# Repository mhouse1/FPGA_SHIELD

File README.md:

# FPGA_SHIELD
An awsome shield that supports multiple tranceivers

* Main schematic view

* board layout

* board model view 1

* board model view 2

* control board with relays

* assembled

* lora radios

note: must adjust converters before powering on level shifting circuit, burned out the chip forgetting that on the first board.

changes for next version:
* xt60 wrong polarity
* ~~usb wrong polarity~~
* ~~usb flush mounting ( add holes for protruding USB pins)~~
* adjust J3 position (De nano power input)
* adjust JP2 position 
* add footprint for non PCB XT60
* adjust J6, J7, J10, J1, J2 position spacing to be same as J15, and J16 that way two or 3 position screw terminals can be used
* replace tantlum capacitors with ceramic capacitors?, replace with surface mount caps for easier assembly
* replace with surface mount resistors 
* move J11 and U8 to above JP1 so relay module is inline with PCB giving an overall smaller footprint for control board.
remove JP3
* delete/remove lora module
* add LM1085ISX-ADJ/NOPB or something similar for regulating power going to the USB converter
* add mini fuse, use keystone 3568
* replace terminal blocks with ED100/2DS	,

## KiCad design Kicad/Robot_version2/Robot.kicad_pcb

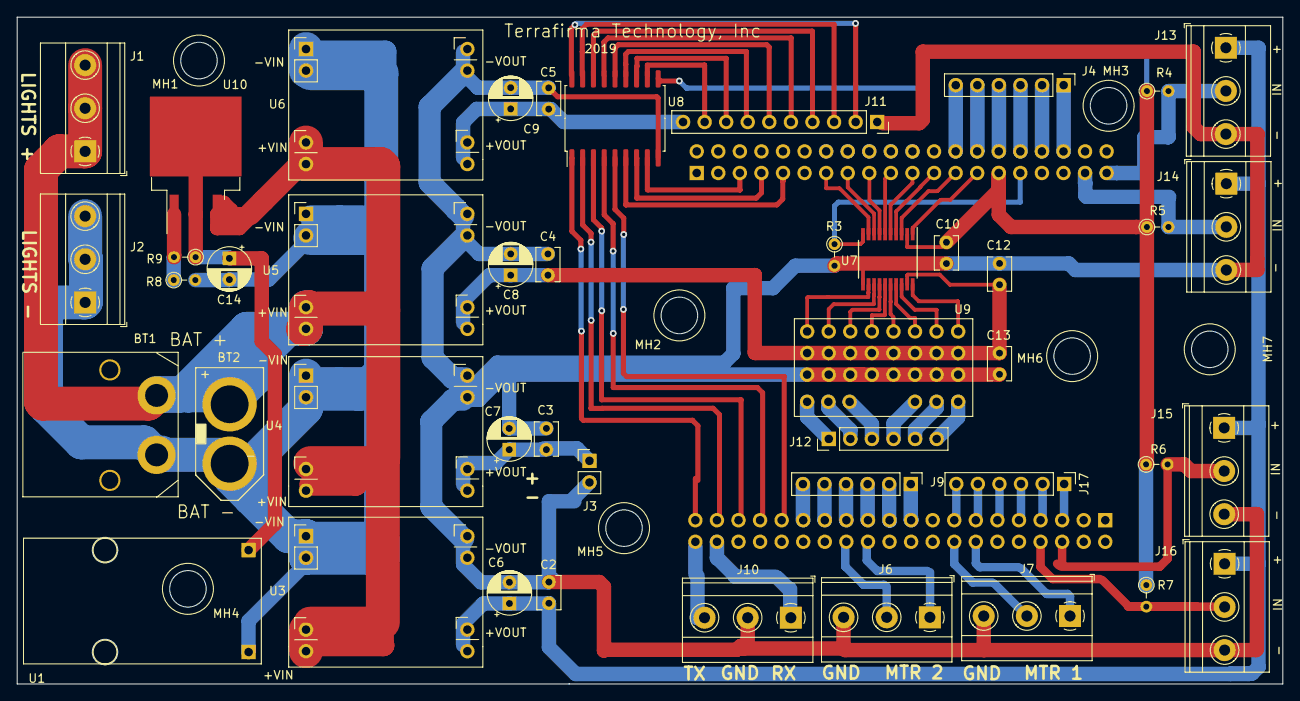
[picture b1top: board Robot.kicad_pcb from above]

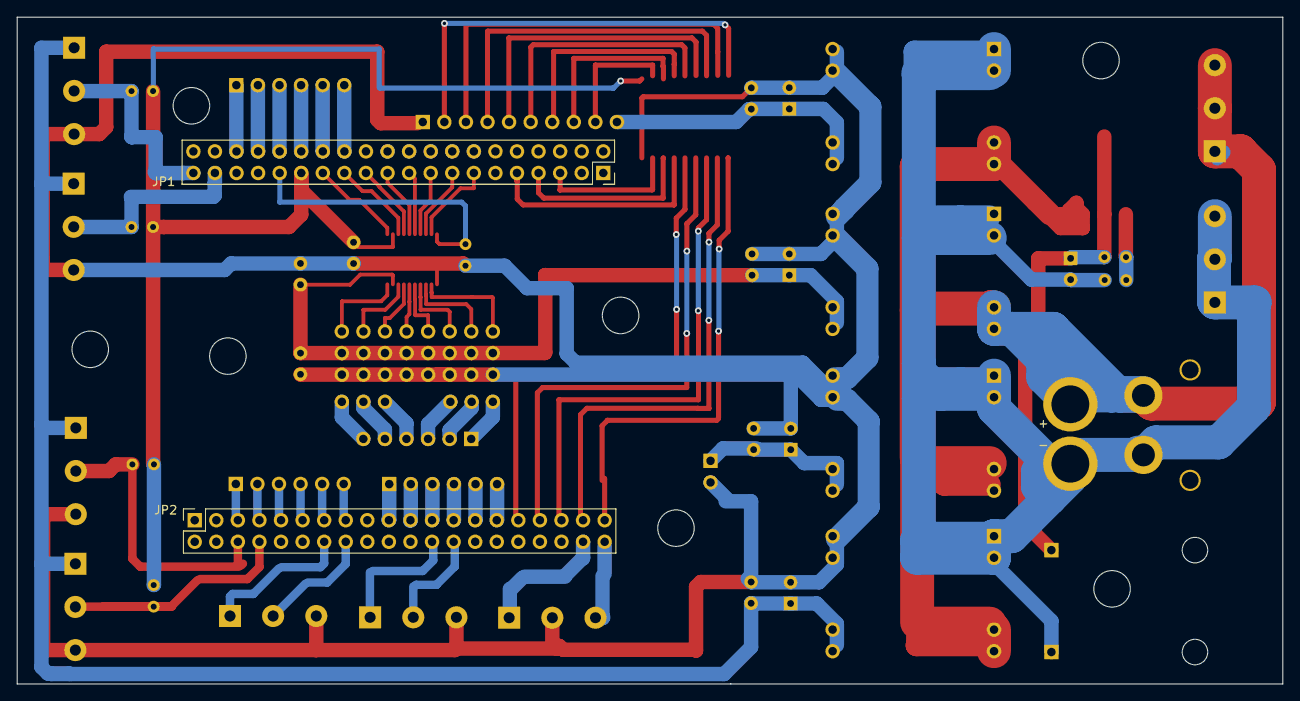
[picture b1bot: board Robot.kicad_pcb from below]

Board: 2 copper layers, 149.0 x 78.5 mm, 54 parts (2 on the bottom side), 77 nets.

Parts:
BT1: Battery_Cell; XT60PW
BT2: Battery_Cell; XT60_M
C2, C3, C4, C5, C10, C12, C13: .1uf; C_Disc_D3.8mm_W2.6mm_P2.50mm
C6, C7, C8, C9, C14: CP1; CP_Radial_D5.0mm_P2.50mm
J1: PositiveBus; TerminalBlock_Phoenix_MKDS-1,5-3-5.08_1x03_P5.08mm_Horizont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
J2: NegativeBus; TerminalBlock_Phoenix_MKDS-1,5-3-5.08_1x03_P5.08mm_Horizont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
J3: PIN HEADER DE0-NANO POWER; PinHeader_1x02_P2.54mm_Vertical
J4, J9, J17: BreakoutHeader; PinHeader_1x06_P2.54mm_Vertical
J6: MotorDriver1; TerminalBlock_Phoenix_MKDS-1,5-3-5.08_1x03_P5.08mm_Horizont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
J7: MotorDriver2; TerminalBlock_Phoenix_MKDS-1,5-3-5.08_1x03_P5.08mm_Horizont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
J10: LORA; TerminalBlock_Phoenix_MKDS-1,5-3-5.08_1x03_P5.08mm_Horizont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
J11: RELAY HEADER; PinSocket_1x10_P2.54mm_Vertical
J12: X8R HEADER; PinHeader_1x06_P2.54mm_Vertical
J13: SENSOR 1; TerminalBlock_Phoenix_MKDS-1,5-3-5.08_1x03_P5.08mm_Horizont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
J14: SENSOR 2; TerminalBlock_Phoenix_MKDS-1,5-3-5.08_1x03_P5.08mm_Horizont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
J15: SENSOR 3; TerminalBlock_Phoenix_MKDS-1,5-3-5.08_1x03_P5.08mm_Horizont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
J16: SENSOR 4; TerminalBlock_Phoenix_MKDS-1,5-3-5.08_1x03_P5.08mm_Horizont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
JP1, JP2: Altera 40 pin connector; PinSocket_2x20_P2.54mm_Vertical
MH1, MH2, MH3, MH4, MH5, MH6, MH7: MountingHole; MountingHole_4.3mm_M4
R3, R4, R5, R6, R7, R8, R9: 4.7K; R_Axial_DIN0204_L3.6mm_D1.6mm_P2.54mm_Vertical
U1: USB_POWER; USB_POWER_flush
U3, U4, U5, U6: Generic_DC_to_DC_Module; GEN_DC_TO_DC
U7: TXS0108E; TSSOP-20_4.4x6.5mm_P0.65mm
U8: TDB62381A; SOIC-18W_7.5x11.6mm_P1.27mm
U9: X8R_Receiver; X8R
U10: LM1085-ADJ; TO-263-3_TabPin2

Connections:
GND: C2.2, C3.2, C4.2, C5.2, C6.2, C7.2, C8.2, C9.2, C10.2, C12.2, C13.2, J3.2, J6.3, J7.3, J10.2, J11.1, J13.3, J14.3, J15.3, J16.3, R3.2, U3.5, U3.6, U4.5, U4.6, U5.5, U5.6, U6.5, U6.6, U7.11, U8.9, U9.17, U9.18, U9.19, U9.20, U9.21, U9.22, U9.23, U9.24
unnamed: BT1.1, BT2.1, C14.2, J2.1, J2.2, J2.3, R8.2, U1.2, U3.1, U3.2, U4.1, U4.2, U5.1, U5.2, U6.1, U6.2
unnamed: BT1.2, BT2.2, J1.1, J1.2, J1.3, U3.3, U3.4, U4.3, U4.4, U5.3, U5.4, U6.3, U6.4, U10.3
unnamed: C3.1, C7.1, J3.1, U4.7, U4.8
unnamed: C14.1, R9.1, U1.1, U10.2
unnamed: J4.1, JP1.36
unnamed: J4.2, JP1.34
unnamed: J4.3, JP1.32
unnamed: J4.4, JP1.30
unnamed: J4.5, JP1.28
unnamed: J4.6, JP1.26
unnamed: J6.1, JP2.14
unnamed: J6.2, JP2.16
unnamed: J7.1, JP2.24
unnamed: J7.2, JP2.26
unnamed: J9.1, JP2.19
unnamed: J9.2, JP2.21
unnamed: J9.3, JP2.23
unnamed: J9.4, JP2.25
unnamed: J9.5, JP2.27
unnamed: J9.6, JP2.29
unnamed: J11.2, U8.18
unnamed: J11.3, U8.17
unnamed: J11.4, U8.16
unnamed: J11.5, U8.15
unnamed: J11.6, U8.14
unnamed: J11.7, U8.13
unnamed: J11.8, U8.12
unnamed: J11.9, U8.11
unnamed: J12.1, U9.25
unnamed: J12.2, U9.26
unnamed: J12.3, U9.27
unnamed: J12.4, U9.28
unnamed: J12.5, U9.29
unnamed: J12.6, U9.30
unnamed: J17.1, JP2.5
unnamed: J17.2, JP2.7
unnamed: J17.3, JP2.9
unnamed: J17.4, JP2.11
unnamed: J17.5, JP2.13
unnamed: J17.6, JP2.15
unnamed: JP1.13, U7.9
unnamed: JP1.15, U7.8
unnamed: JP1.17, U7.7
unnamed: JP1.19, U7.6
unnamed: JP1.21, U7.5
unnamed: JP1.23, U7.4
unnamed: JP1.25, U7.3
unnamed: JP1.27, U7.1
unnamed: JP1.31, R3.1, U7.10
unnamed: R8.1, R9.2, U10.1
unnamed: U7.12, U9.1
unnamed: U7.13, U9.2
unnamed: U7.14, U9.3
unnamed: U7.15, U9.4
unnamed: U7.16, U9.5
unnamed: U7.17, U9.6
unnamed: U7.18, U9.7
unnamed: U7.20, U9.8
PWR_8CH_RLY: C5.1, C9.1, J11.10, U6.7, U6.8
PWR_8XR: C4.1, C8.1, C12.1, C13.1, U5.7, U5.8, U7.19, U9.9, U9.10, U9.11, U9.12, U9.13, U9.14, U9.15, U9.16
PWR_IND_SENSOR: C2.1, C6.1, J13.1, J14.1, J15.1, J16.1, U3.7, U3.8
RI1: JP2.39, U8.1
RI2: JP2.37, U8.2
RI3: JP2.35, U8.3
RI4: JP2.33, U8.4
RI5: JP2.31, U8.5
RI6: JP1.9, U8.6
RI7: JP1.7, U8.7
RI8: JP1.5, U8.8
RX: J10.1, JP2.38
SENSOR1: J13.2, JP1.39, R4.2
SENSOR2: J14.2, JP1.37, R5.2
SENSOR3: J15.2, JP2.6, R6.2
SENSOR4: J16.2, JP2.8, R7.2
TX: J10.3, JP2.40
VCC3P3: C10.1, JP1.29, R4.1, R5.1, R6.1, R7.1, U7.2, U8.10

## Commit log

2019-10-03 initial schematic
2019-10-03 updated naming
2019-10-03 updated schematic picture
2019-10-04 ADDED 3 PIN TERMINALS AND A NEW DRIVER RELAY
    ADDED 3 PIN TERMINALS AND NEW DRIVER FOR THE RELAY
2019-10-04 added screw terminals for lights and motor driver signals
2019-10-04 added LoRa module, connected 3.3v pullup to JP1, removed duplicate inductive sensor terminals
2019-10-07 All the decals are done. Need to discuss tommow power for LORA and x8R chip before starting to place and route the PCB
    All the decals are done.
    Need to discuss tommow power for LORA and x8R chip before starting to place and route the PCB
2019-10-08 UPDATE PS JUMPER AND LEVEL SHIFTER
2019-10-08 UPDATED PARTS ON PCB
2019-10-08 add decoupling caps
    added decoupling caps
2019-10-08 add sip resistor
2019-10-09 updates 2x20 header decal
2019-10-09 latest view
2019-10-10 fixed relay driver OE pin map, added breakout for unused pins, J15 and J16 are now + and - bus terminals
2019-10-11 fixed 2 pullups and added cap on output of dc to dc
2019-10-11 placed header
2019-10-13 Parts placement plus other changes
    parts placement plus other changes
2019-10-13 changes
    changes
2019-10-13 layout complete for review
    layout complete for review
2019-10-13 added mounting holes
    add mounting holes
2019-10-14 fixed fpga power input and jp2 header, usb pad positions, added some more mounting holes
2019-10-15 updated position of a few components on the board, generated output gerber files for first production
2019-10-16 first release board documentation
2019-10-16 Update README.md
    updated pics
2019-11-06 fixed usb polarity, added usb 3d model, edited usb footprin for flush mounting, updated pictures
2019-11-06 updated usb foot print to remove copper from through holes
2019-11-19 updated changes requested for V2 board
2019-11-19 updated picture of board
2019-11-23 version2
2019-11-23 added picture of relocated relay board diagram
2019-11-23 added drawing of general area for relay header
2019-11-23 rev 2 placement
2019-11-23 First draft of rev2
2019-11-24 fixed usb
2019-11-24 moved parts closer
2019-11-26 moved ref
2019-12-14 updated schematic and layout for shield v2
2019-12-14 updated picture of board, layout, and schematic
2020-01-08 added BOM, and minor updates
2020-01-08 updated pictures
2020-01-12 moved jp2 and j3 -0.3X and -0.15Y
